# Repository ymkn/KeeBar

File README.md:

# KeeBar S

A 40%-sized, horizontally elongated with centerized numkeys mechanical keyboard.

## Default Layout

You can also customize the layout using [Vial](https://get.vial.today/).

## Build Guide

See [Build Guide](doc/buildguide_s.md).

## License

This project is licensed under the MIT License, see the [LICENSE file](LICENSE) for details.

However, this does not apply to logo data (image files, KiCAD footprints, etc.) included in the resources of this project. Please contact us for secondary use.

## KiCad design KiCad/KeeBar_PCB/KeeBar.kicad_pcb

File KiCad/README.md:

# KiCAD source files

## KiCAD version

7.x or higher is required.

## dependencies

### KiCAD plugins

- Keyswitch Kicad Library com.github.perigoso.keyswitch-kicad-library 2.4
  - Keyswitch and Stab

### external libraries

- https://github.com/crides/kleeb
  - rp2040-zero symbol & footprint
- https://github.com/Salicylic-acid3/KiCAD_FootPrint
  - M2 mounting hole footprint
  - Keyswitch plate mounting hole footprint

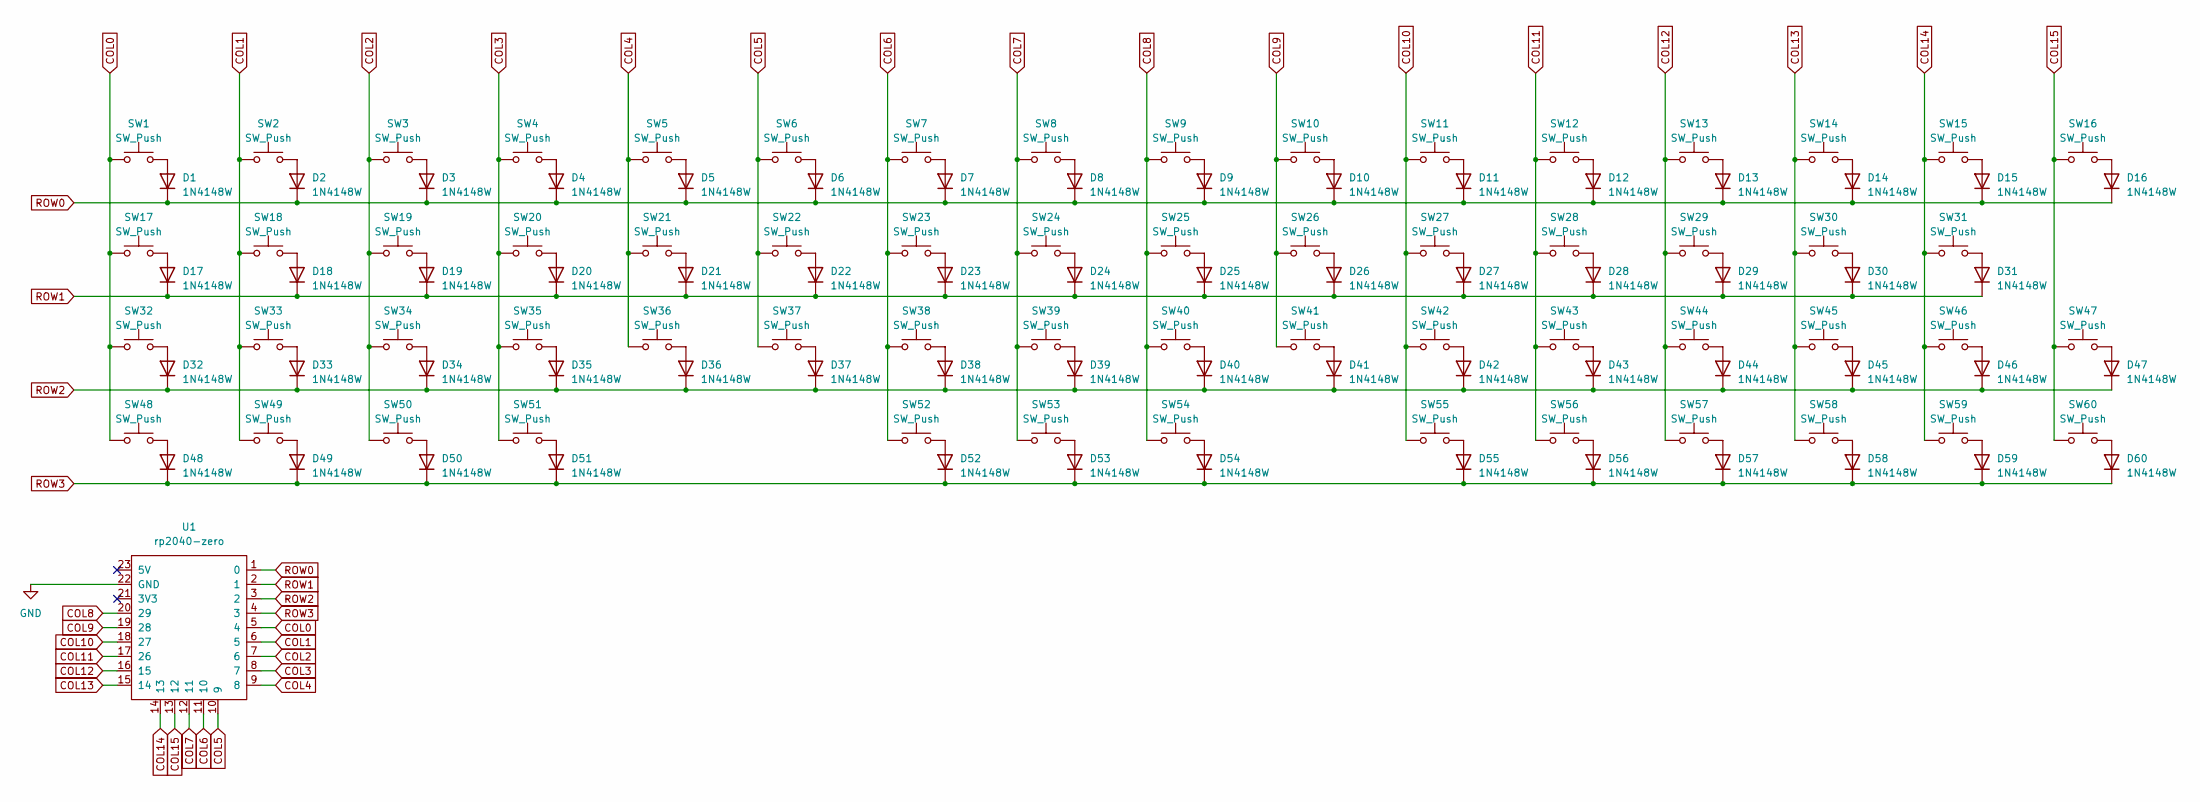
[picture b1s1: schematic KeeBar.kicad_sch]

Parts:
D1, D2, D3, D4, D5, D6, D7, D8, D9, D10, D11, D12, D13, D14, D15, D16, D17, D18, D19, D20, D21, D22, D23, D24, D25, D26, D27, D28, D29, D30, D31, D32, D33, D34, D35, D36, D37, D38, D39, D40, D41, D42, D43, D44, D45, D46, D47, D48, D49, D50, D51, D52, D53, D54, D55, D56, D57, D58, D59, D60: 1N4148W; D_SOD-123
SW1, SW15, SW48, SW53: SW_Push; MXOnly-1.5U-Hotswap
SW2, SW3, SW4, SW5, SW6, SW7, SW8, SW9, SW10, SW11, SW12, SW13, SW14, SW16, SW18, SW19, SW20, SW21, SW22, SW23, SW24, SW25, SW26, SW27, SW28, SW29, SW30, SW33, SW34, SW35, SW36, SW37, SW38, SW39, SW40, SW41, SW42, SW43, SW44, SW45, SW47, SW49, SW58, SW59, SW60: SW_Push; MXOnly-1U-Hotswap
SW17: SW_Push; MXOnly-1.75U-Hotswap
SW31: SW_Push; MXOnly-2.25U-Hotswap
SW32: SW_Push; MXOnly-2U-Hotswap
SW46, SW50, SW51, SW55, SW56, SW57: SW_Push; MXOnly-1.25U-Hotswap
SW52, SW54: SW_Push; MXOnly-2.75U-Hotswap
U1: rp2040-zero; rp2040-zero-tht

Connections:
COL0: SW1.1, SW17.1, SW32.1, SW48.1, U1.5 (4)
COL1: SW2.1, SW18.1, SW33.1, SW49.1, U1.6 (5)
COL2: SW3.1, SW19.1, SW34.1, SW50.1, U1.7 (6)
COL3: SW4.1, SW20.1, SW35.1, SW51.1, U1.8 (7)
COL4: SW5.1, SW21.1, SW36.1, U1.9 (8)
COL5: SW6.1, SW22.1, SW37.1, U1.10 (9)
COL6: SW7.1, SW23.1, SW38.1, SW52.1, U1.11 (10)
COL7: SW8.1, SW24.1, SW39.1, SW53.1, U1.12 (11); also elsewhere on the board
COL8: SW9.1, SW25.1, SW40.1, SW54.1, U1.20 (29)
COL9: SW10.1, SW26.1, SW41.1, U1.19 (28)
COL10: SW11.1, SW27.1, SW42.1, SW55.1, U1.18 (27)
COL11: SW12.1, SW28.1, SW43.1, SW56.1, U1.17 (26)
COL12: SW13.1, SW29.1, SW44.1, SW57.1, U1.16 (15)
COL13: SW14.1, SW30.1, SW45.1, SW58.1, U1.15 (14)
COL14: SW15.1, SW31.1, SW46.1, SW59.1, U1.14 (13); also elsewhere on the board
COL15: SW16.1, SW47.1, SW60.1, U1.13 (12); also elsewhere on the board
GND: U1.22 (GND)
unnamed: D1.2 (A), SW1.2
unnamed: D2.2 (A), SW2.2
unnamed: D3.2 (A), SW3.2
unnamed: D4.2 (A), SW4.2
unnamed: D5.2 (A), SW5.2
unnamed: D6.2 (A), SW6.2
unnamed: D7.2 (A), SW7.2
unnamed: D8.2 (A), SW8.2
unnamed: D9.2 (A), SW9.2
unnamed: D10.2 (A), SW10.2
unnamed: D11.2 (A), SW11.2
unnamed: D12.2 (A), SW12.2
unnamed: D13.2 (A), SW13.2
unnamed: D14.2 (A), SW14.2
unnamed 31: D15.2 (A), SW15.2; also elsewhere on the board
unnamed 32: D16.2 (A), SW16.2; also elsewhere on the board
unnamed: D17.2 (A), SW17.2
unnamed: D18.2 (A), SW18.2
unnamed: D19.2 (A), SW19.2
unnamed: D20.2 (A), SW20.2
unnamed: D21.2 (A), SW21.2
unnamed: D22.2 (A), SW22.2
unnamed: D23.2 (A), SW23.2
unnamed: D24.2 (A), SW24.2
unnamed: D25.2 (A), SW25.2
unnamed: D26.2 (A), SW26.2
unnamed: D27.2 (A), SW27.2
unnamed: D28.2 (A), SW28.2
unnamed: D29.2 (A), SW29.2
unnamed: D30.2 (A), SW30.2
unnamed: D31.2 (A), SW31.2
unnamed: D32.2 (A), SW32.2
unnamed: D33.2 (A), SW33.2
unnamed: D34.2 (A), SW34.2
unnamed: D35.2 (A), SW35.2
unnamed: D36.2 (A), SW36.2
unnamed: D37.2 (A), SW37.2
unnamed: D38.2 (A), SW38.2
unnamed: D39.2 (A), SW39.2
unnamed: D40.2 (A), SW40.2
unnamed: D41.2 (A), SW41.2
unnamed: D42.2 (A), SW42.2
unnamed: D43.2 (A), SW43.2
unnamed: D44.2 (A), SW44.2
unnamed: D45.2 (A), SW45.2
unnamed: D46.2 (A), SW46.2
unnamed: D47.2 (A), SW47.2
unnamed: D48.2 (A), SW48.2
unnamed: D49.2 (A), SW49.2
unnamed: D50.2 (A), SW50.2
unnamed: D51.2 (A), SW51.2
unnamed: D52.2 (A), SW52.2
unnamed 69: D53.2 (A), SW53.2; also elsewhere on the board
unnamed: D54.2 (A), SW54.2
unnamed: D55.2 (A), SW55.2
unnamed: D56.2 (A), SW56.2
unnamed: D57.2 (A), SW57.2
unnamed: D58.2 (A), SW58.2
unnamed: D59.2 (A), SW59.2
unnamed: D60.2 (A), SW60.2
ROW0: D1.1 (K), D2.1 (K), D3.1 (K), D4.1 (K), D5.1 (K), D6.1 (K), D7.1 (K), D8.1 (K), D9.1 (K), D10.1 (K), D11.1 (K), D12.1 (K), D13.1 (K), D14.1 (K), D15.1 (K), D16.1 (K), U1.1 (0)
ROW1: D17.1 (K), D18.1 (K), D19.1 (K), D20.1 (K), D21.1 (K), D22.1 (K), D23.1 (K), D24.1 (K), D25.1 (K), D26.1 (K), D27.1 (K), D28.1 (K), D29.1 (K), D30.1 (K), D31.1 (K), U1.2 (1)
ROW2: D32.1 (K), D33.1 (K), D34.1 (K), D35.1 (K), D36.1 (K), D37.1 (K), D38.1 (K), D39.1 (K), D40.1 (K), D41.1 (K), D42.1 (K), D43.1 (K), D44.1 (K), D45.1 (K), D46.1 (K), D47.1 (K), U1.3 (2)
ROW3: D48.1 (K), D49.1 (K), D50.1 (K), D51.1 (K), D52.1 (K), D53.1 (K), D54.1 (K), D55.1 (K), D56.1 (K), D57.1 (K), D58.1 (K), D59.1 (K), D60.1 (K), U1.4 (3)

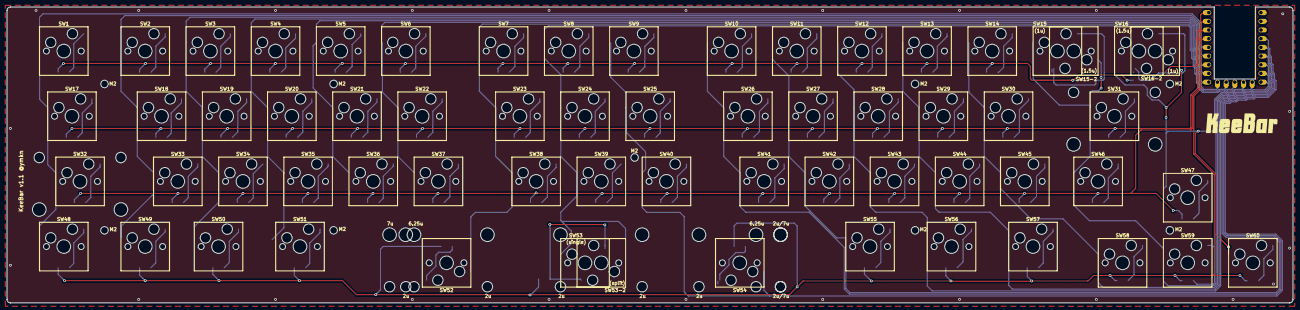
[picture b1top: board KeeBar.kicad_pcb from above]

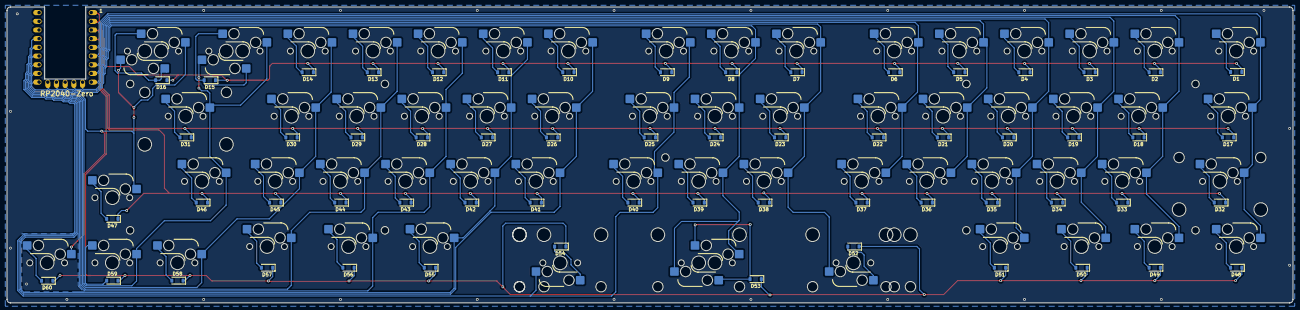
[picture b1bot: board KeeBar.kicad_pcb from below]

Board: 2 copper layers, 376.0 x 86.5 mm, 133 parts (61 on the bottom side), 80 nets.

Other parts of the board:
M2_1, M2_2, M2_3, M2_4, M2_5, M2_6, M2_7, M2_8, M2_9: Val**; m2_Screw_Hole
SW15-2: SW_Push; SW_Hotswap_Kailh_MX_1.50u
SW16-2: SW_Push; SW_Hotswap_Kailh_MX_1.00u
SW53-2: SW_Push; SW_Hotswap_Kailh_MX_2.00u

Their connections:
COL7: SW53-2.1; also elsewhere on the board
COL14: SW15-2.1; also elsewhere on the board
COL15: SW16-2.1; also elsewhere on the board
unnamed 31: SW15-2.2; also elsewhere on the board
unnamed 32: SW16-2.2; also elsewhere on the board
unnamed 69: SW53-2.2; also elsewhere on the board

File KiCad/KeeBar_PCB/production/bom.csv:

Designator,Footprint,Quantity,Value,LCSC Part #
"D1, D10, D11, D12, D13, D14, D15, D16, D17, D18, D19, D2, D20, D21, D22, D23, D24, D25, D26, D27, D28, D29, D3, D30, D31, D32, D33, D34, D35, D36, D37, D38, D39, D4, D40, D41, D42, D43, D44, D45, D46, D47, D48, D49, D5, D50, D51, D52, D53, D54, D55, D56, D57, D58, D59, D6, D60, D7, D8, D9",D_SOD-123,60,1N4148W,
"SW1, SW15, SW48, SW53",SW_Hotswap_Kailh_MX_1.50u,4,SW_Push,
"SW10, SW11, SW12, SW13, SW14, SW16, SW18, SW19, SW2, SW20, SW21, SW22, SW23, SW24, SW25, SW26, SW27, SW28, SW29, SW3, SW30, SW33, SW34, SW35, SW36, SW37, SW38, SW39, SW4, SW40, SW41, SW42, SW43, SW44, SW45, SW47, SW49, SW5, SW58, SW59, SW6, SW60, SW7, SW8, SW9",SW_Hotswap_Kailh_MX_1.00u,45,SW_Push,
SW17,SW_Hotswap_Kailh_MX_1.75u,1,SW_Push,
SW31,SW_Hotswap_Kailh_MX_2.25u,1,SW_Push,
SW32,SW_Hotswap_Kailh_MX_2.00u,1,SW_Push,
"SW46, SW50, SW51, SW55, SW56, SW57",SW_Hotswap_Kailh_MX_1.25u,6,SW_Push,
"SW52, SW54",SW_Hotswap_Kailh_MX_2.75u,2,SW_Push,
U1,rp2040-zero-tht,1,rp2040-zero,

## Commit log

2023-06-19 First order version
2023-10-14 ケース発注時点
2023-10-14 寸法記入
2023-10-28 ケースデータの誤りに関する注意書きを追加
2023-11-04 USBコネクタ口の干渉について注意書き追加
2023-11-16 QMKファームウェアの登録（Vial対応）
2023-12-06 VID/PIDの修正
2023-12-09 ネジ穴位置の誤りを修正、USBコネクタ口を拡大
2023-12-09 写真の差し替え、日本語キーマップファイルの追加
2023-12-15 画像ディレクトリの名称変更
2023-12-15 ビルドガイドを追加
2023-12-15 レイアウト画像のリンク修正
2023-12-16 同梱ネジ数を修正
2023-12-21 USB穴の修正
2023-12-22 太めのスペーサーでも通るようにアクリルプレートの穴径を拡張
2023-12-22 リソースのダウンロード先をリリース断面に変更
2023-12-22 誤記修正
2023-12-28 kleebをsubmoduleとして追加
2023-12-29 外部ライブラリをSubmoduleで参照するように変更
2023-12-29 ロゴに関するライセンスの例外追加、依存ライブラリの情報更新、レイアウト画像の更新
2023-12-29 gitignoreの導入
2023-12-29 自前のライブラリの場所を統合
2023-12-29 v1.1設計の更新
2024-01-02 1.1発注断面
2024-01-03 FreeCADのgitignoreを追加
2024-01-03 v1.1のケースを作成
2024-01-06 PCBフォーム用KiCADデータ
2024-01-06 スタビ用の穴をあけ忘れていたのを修正
2024-01-10 プレートのスペースバー位置がずれていたのを修正
2024-01-10 動作確認用のPRK Firmwareを追加
2024-01-11 高さの誤りと底面ネジ穴の位置が上下反転していたのを修正
2024-01-21 USB穴の位置を微調整
2024-01-21 Enterに重なっていた不要なオブジェクトを削除
2024-01-21 ファームウェアのレイアウト見た目を1.1相当に更新
2024-01-21 v1.1用ビルドガイドの更新
2024-02-07 SW54と6.25uスタビライザー干渉について追記
2024-02-18 SW54のソケット干渉についてGeteronソケットによる回避を追記、他のRP2040機器接続時の初期動作について追記
